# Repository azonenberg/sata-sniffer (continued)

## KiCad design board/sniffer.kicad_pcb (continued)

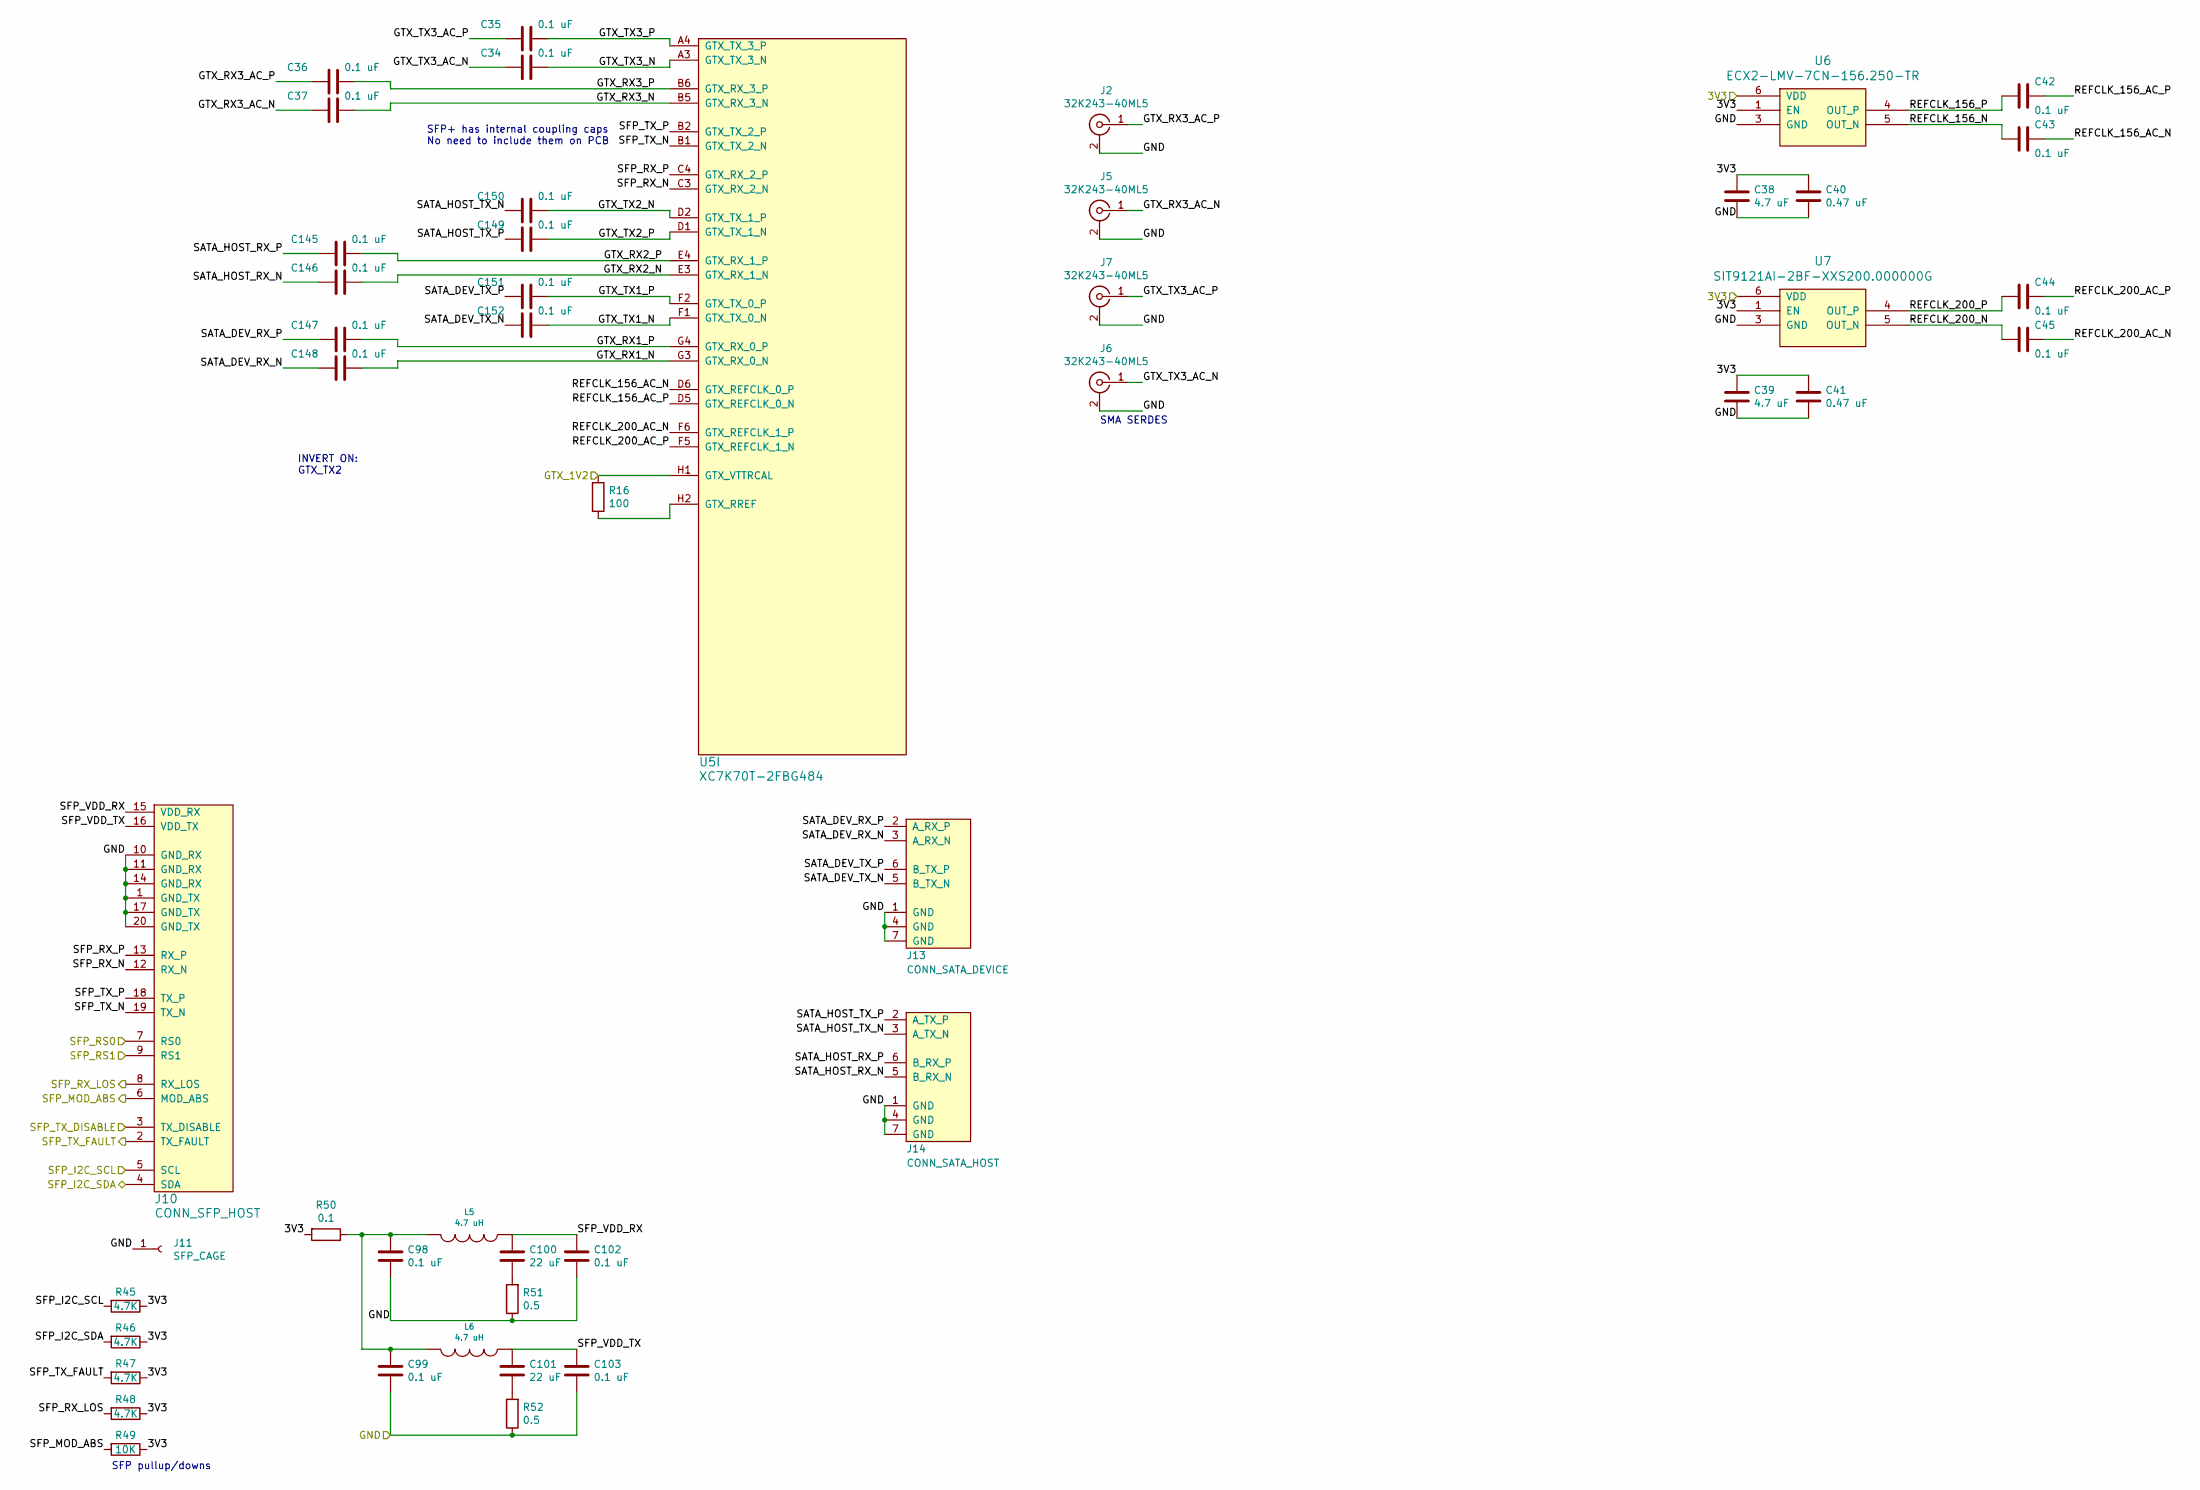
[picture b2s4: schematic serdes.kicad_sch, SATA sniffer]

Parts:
C34, C35, C36, C37, C42, C43, C44, C45, C98, C99, C102, C103, C145, C146, C147, C148, C149, C150, C151, C152: 0.1 uF; EIA_0402_CAP_NOSILK
C38, C39: 4.7 uF; EIA_0603_CAP_NOSILK
C40, C41: 0.47 uF; EIA_0402_CAP_NOSILK
C100, C101: 22 uF; EIA_1206_CAP_NOSILK
J2, J5, J6, J7: 32K243-40ML5; CONN_SMA_EDGE_ROSENBERGER_32K243_40ML5
J10: CONN_SFP_HOST; CONN_SFP+_AMPHENOL_UE76_A10_2000T
J11: SFP_CAGE; CONN_SFP_CAGE_TE_2007194-1
J13: CONN_SATA_DEVICE; CONN_SATA_MOLEX_0674901220
J14: CONN_SATA_HOST; CONN_SATA_MOLEX_0674901220
L5, L6: 4.7 uH; EIA_0805_INDUCTOR_NOSILK
R16: 100; EIA_0402_RES_NOSILK
R45, R46, R47, R48: 4.7K; EIA_0402_RES_NOSILK
R49: 10K; EIA_0402_RES_NOSILK
R50: 0.1; EIA_0402_RES_NOSILK
R51, R52: 0.5; EIA_0402_RES_NOSILK
U5: XC7K70T-2FBG484; BGA_484_22x22_FULLARRAY_1MM
U6: ECX2-LMV-7CN-156.250-TR; OSCILLATOR_LVDS_7.0x5.0
U7: SIT9121AI-2BF-XXS200.000000G; OSCILLATOR_LVDS_3.2x2.5

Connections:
/3.3V I/O/SFP_MOD_ABS: J10.6 (MOD_ABS), R49.2; also elsewhere on the board
/3.3V I/O/SFP_RS0: J10.7 (RS0); also elsewhere on the board
/3.3V I/O/SFP_RS1: J10.9 (RS1); also elsewhere on the board
/3.3V I/O/SFP_RX_LOS: J10.8 (RX_LOS), R48.2; also elsewhere on the board
/3.3V I/O/SFP_TX_DISABLE: J10.3 (TX_DISABLE); also elsewhere on the board
/3.3V I/O/SFP_TX_FAULT: J10.2 (TX_FAULT), R47.2; also elsewhere on the board
/3V3: C38.1, C39.1, C40.1, C41.1, R45.1, R46.1, R47.1, R48.1, R49.1, R50.2, U6.1 (EN), U6.6 (VDD), U7.1 (EN), U7.6 (VDD); also elsewhere on the board
/GTX_1V2: R16.1, U5.H1 (GTX_VTTRCAL); also elsewhere on the board
/SERDES interfaces/GTX_RX1_N: C148.1, U5.G3 (GTX_RX_0_N)
/SERDES interfaces/GTX_RX1_P: C147.1, U5.G4 (GTX_RX_0_P)
/SERDES interfaces/GTX_RX2_N: C146.1, U5.E3 (GTX_RX_1_N)
/SERDES interfaces/GTX_RX2_P: C145.1, U5.E4 (GTX_RX_1_P)
/SERDES interfaces/GTX_RX3_AC_N: C37.2, J5.1 (In)
/SERDES interfaces/GTX_RX3_AC_P: C36.2, J2.1 (In)
/SERDES interfaces/GTX_RX3_N: C37.1, U5.B5 (GTX_RX_3_N)
/SERDES interfaces/GTX_RX3_P: C36.1, U5.B6 (GTX_RX_3_P)
/SERDES interfaces/GTX_TX1_N: C152.1, U5.F1 (GTX_TX_0_N)
/SERDES interfaces/GTX_TX1_P: C151.1, U5.F2 (GTX_TX_0_P)
/SERDES interfaces/GTX_TX2_N: C150.1, U5.D2 (GTX_TX_1_P)
/SERDES interfaces/GTX_TX2_P: C149.1, U5.D1 (GTX_TX_1_N)
/SERDES interfaces/GTX_TX3_AC_N: C34.2, J6.1 (In)
/SERDES interfaces/GTX_TX3_AC_P: C35.2, J7.1 (In)
/SERDES interfaces/GTX_TX3_N: C34.1, U5.A3 (GTX_TX_3_N)
/SERDES interfaces/GTX_TX3_P: C35.1, U5.A4 (GTX_TX_3_P)
/SERDES interfaces/REFCLK_156_AC_N: C43.1, U5.D6 (GTX_REFCLK_0_P)
/SERDES interfaces/REFCLK_156_AC_P: C42.1, U5.D5 (GTX_REFCLK_0_N)
/SERDES interfaces/REFCLK_156_N: C43.2, U6.5 (OUT_N)
/SERDES interfaces/REFCLK_156_P: C42.2, U6.4 (OUT_P)
/SERDES interfaces/REFCLK_200_AC_N: C45.1, U5.F6 (GTX_REFCLK_1_P)
/SERDES interfaces/REFCLK_200_AC_P: C44.1, U5.F5 (GTX_REFCLK_1_N)
/SERDES interfaces/REFCLK_200_N: C45.2, U7.5 (OUT_N)
/SERDES interfaces/REFCLK_200_P: C44.2, U7.4 (OUT_P)
/SERDES interfaces/SATA_DEV_RX_N: C148.2, J13.3 (A_RX_N)
/SERDES interfaces/SATA_DEV_RX_P: C147.2, J13.2 (A_RX_P)
/SERDES interfaces/SATA_DEV_TX_N: C152.2, J13.5 (B_TX_N)
/SERDES interfaces/SATA_DEV_TX_P: C151.2, J13.6 (B_TX_P)
/SERDES interfaces/SATA_HOST_RX_N: C146.2, J14.5 (B_RX_N)
/SERDES interfaces/SATA_HOST_RX_P: C145.2, J14.6 (B_RX_P)
/SERDES interfaces/SATA_HOST_TX_N: C150.2, J14.3 (A_TX_N)
/SERDES interfaces/SATA_HOST_TX_P: C149.2, J14.2 (A_TX_P)
/SERDES interfaces/SFP_I2C_SCL: J10.5 (SCL), R45.2; also elsewhere on the board
/SERDES interfaces/SFP_I2C_SDA: J10.4 (SDA), R46.2; also elsewhere on the board
/SERDES interfaces/SFP_RX_N: J10.12 (RX_N), U5.C3 (GTX_RX_2_N)
/SERDES interfaces/SFP_RX_P: J10.13 (RX_P), U5.C4 (GTX_RX_2_P)
/SERDES interfaces/SFP_TX_N: J10.19 (TX_N), U5.B1 (GTX_TX_2_N)
/SERDES interfaces/SFP_TX_P: J10.18 (TX_P), U5.B2 (GTX_TX_2_P)
/SERDES interfaces/SFP_VDD_RX: C100.1, C102.1, J10.15 (VDD_RX), L5.1
/SERDES interfaces/SFP_VDD_TX: C101.1, C103.1, J10.16 (VDD_TX), L6.1
unnamed: C98.1, C99.1, L5.2, L6.2, R50.1
unnamed: C100.2, R51.2
unnamed: C101.2, R52.2
unnamed: R16.2, U5.H2 (GTX_RREF)

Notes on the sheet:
SMA SERDES
SFP+ has internal coupling caps No need to include them on PCB
INVERT ON: GTX_TX2
SFP pullup/downs

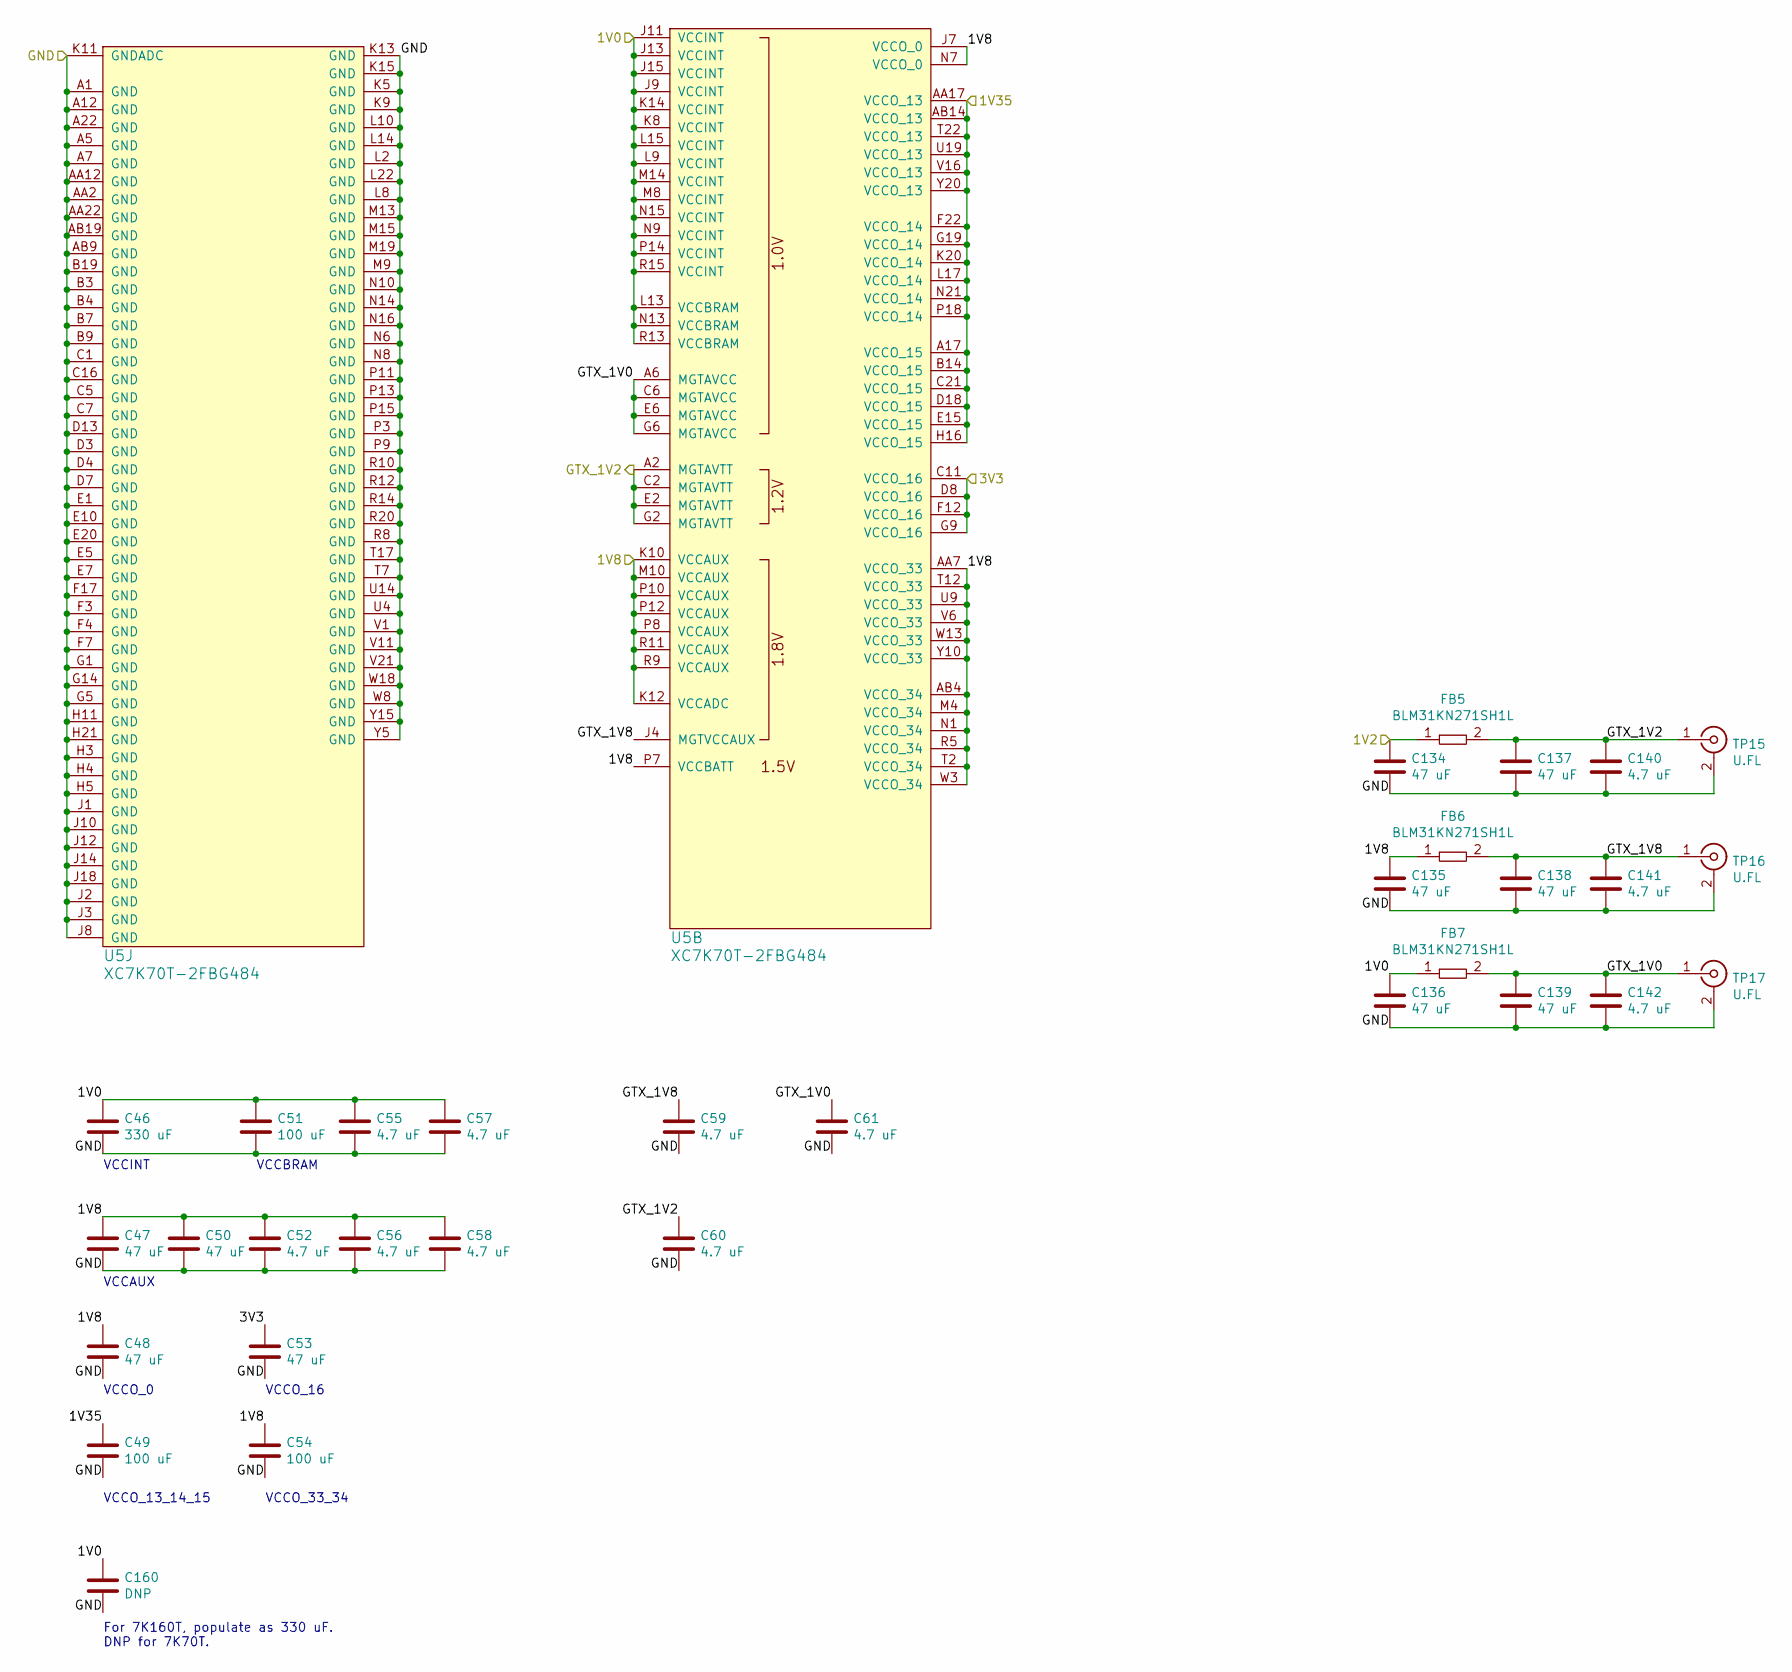
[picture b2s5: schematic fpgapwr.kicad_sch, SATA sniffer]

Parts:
C46: 330 uF; EIA_1210_CAP_NOSILK
C47, C48, C50: 47 uF; EIA_0805_CAP_NOSILK
C49, C51, C54: 100 uF; EIA_1206_CAP_NOSILK
C52, C55, C56, C57, C58, C59, C60, C61, C140, C141, C142: 4.7 uF; EIA_0603_CAP_NOSILK
C53: 47 uF; EIA_1206_CAP_NOSILK
C134, C135, C136, C137, C138, C139: 47 uF; EIA_1210_CAP_NOSILK
C160: DNP; EIA_1210_CAP_NOSILK
FB5, FB6, FB7: BLM31KN271SH1L; EIA_1206_CAP_NOSILK
TP15, TP16, TP17: U.FL; CONN_U.FL_TE_1909763-1
U5: XC7K70T-2FBG484; BGA_484_22x22_FULLARRAY_1MM

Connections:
/1V0: C46.1, C51.1, C55.1, C57.1, C136.1, C160.1, FB7.1, U5.J9 (VCCINT), U5.J11 (VCCINT), U5.J13 (VCCINT), U5.J15 (VCCINT), U5.K8 (VCCINT), U5.K14 (VCCINT), U5.L9 (VCCINT), U5.L13 (VCCBRAM), U5.L15 (VCCINT), U5.M8 (VCCINT), U5.M14 (VCCINT), U5.N9 (VCCINT), U5.N13 (VCCBRAM), U5.N15 (VCCINT), U5.P14 (VCCINT), U5.R13 (VCCBRAM), U5.R15 (VCCINT); also elsewhere on the board
/1V2: C134.1, FB5.1; also elsewhere on the board
/1V8: C47.1, C48.1, C50.1, C52.1, C54.1, C56.1, C58.1, C135.1, FB6.1, U5.AA7 (VCCO_33), U5.AB4 (VCCO_34), U5.J7 (VCCO_0), U5.K10 (VCCAUX), U5.K12 (VCCADC), U5.M4 (VCCO_34), U5.M10 (VCCAUX), U5.N1 (VCCO_34), U5.N7 (VCCO_0), U5.P7 (VCCBATT), U5.P8 (VCCAUX), U5.P10 (VCCAUX), U5.P12 (VCCAUX), U5.R5 (VCCO_34), U5.R9 (VCCAUX), U5.R11 (VCCAUX), U5.T2 (VCCO_34), U5.T12 (VCCO_33), U5.U9 (VCCO_33), U5.V6 (VCCO_33), U5.W3 (VCCO_34), U5.W13 (VCCO_33), U5.Y10 (VCCO_33); also elsewhere on the board
/1V35: C49.1, U5.A17 (VCCO_15), U5.AA17 (VCCO_13), U5.AB14 (VCCO_13), U5.B14 (VCCO_15), U5.C21 (VCCO_15), U5.D18 (VCCO_15), U5.E15 (VCCO_15), U5.F22 (VCCO_14), U5.G19 (VCCO_14), U5.H16 (VCCO_15), U5.K20 (VCCO_14), U5.L17 (VCCO_14), U5.N21 (VCCO_14), U5.P18 (VCCO_14), U5.T22 (VCCO_13), U5.U19 (VCCO_13), U5.V16 (VCCO_13), U5.Y20 (VCCO_13); also elsewhere on the board
/3V3: C53.1, U5.C11 (VCCO_16), U5.D8 (VCCO_16), U5.F12 (VCCO_16), U5.G9 (VCCO_16); also elsewhere on the board
/FPGA power/GTX_1V0: C61.1, C139.1, C142.1, FB7.2, TP17.1 (In), U5.A6 (MGTAVCC), U5.C6 (MGTAVCC), U5.E6 (MGTAVCC), U5.G6 (MGTAVCC)
/FPGA power/GTX_1V8: C59.1, C138.1, C141.1, FB6.2, TP16.1 (In), U5.J4 (MGTVCCAUX)
/GTX_1V2: C60.1, C137.1, C140.1, FB5.2, TP15.1 (In), U5.A2 (MGTAVTT), U5.C2 (MGTAVTT), U5.E2 (MGTAVTT), U5.G2 (MGTAVTT); also elsewhere on the board

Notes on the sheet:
VCCINT
VCCBRAM
VCCO_16
For 7K160T, populate as 330 uF. DNP for 7K70T.
VCCAUX
VCCO_0
VCCO_13_14_15
VCCO_33_34

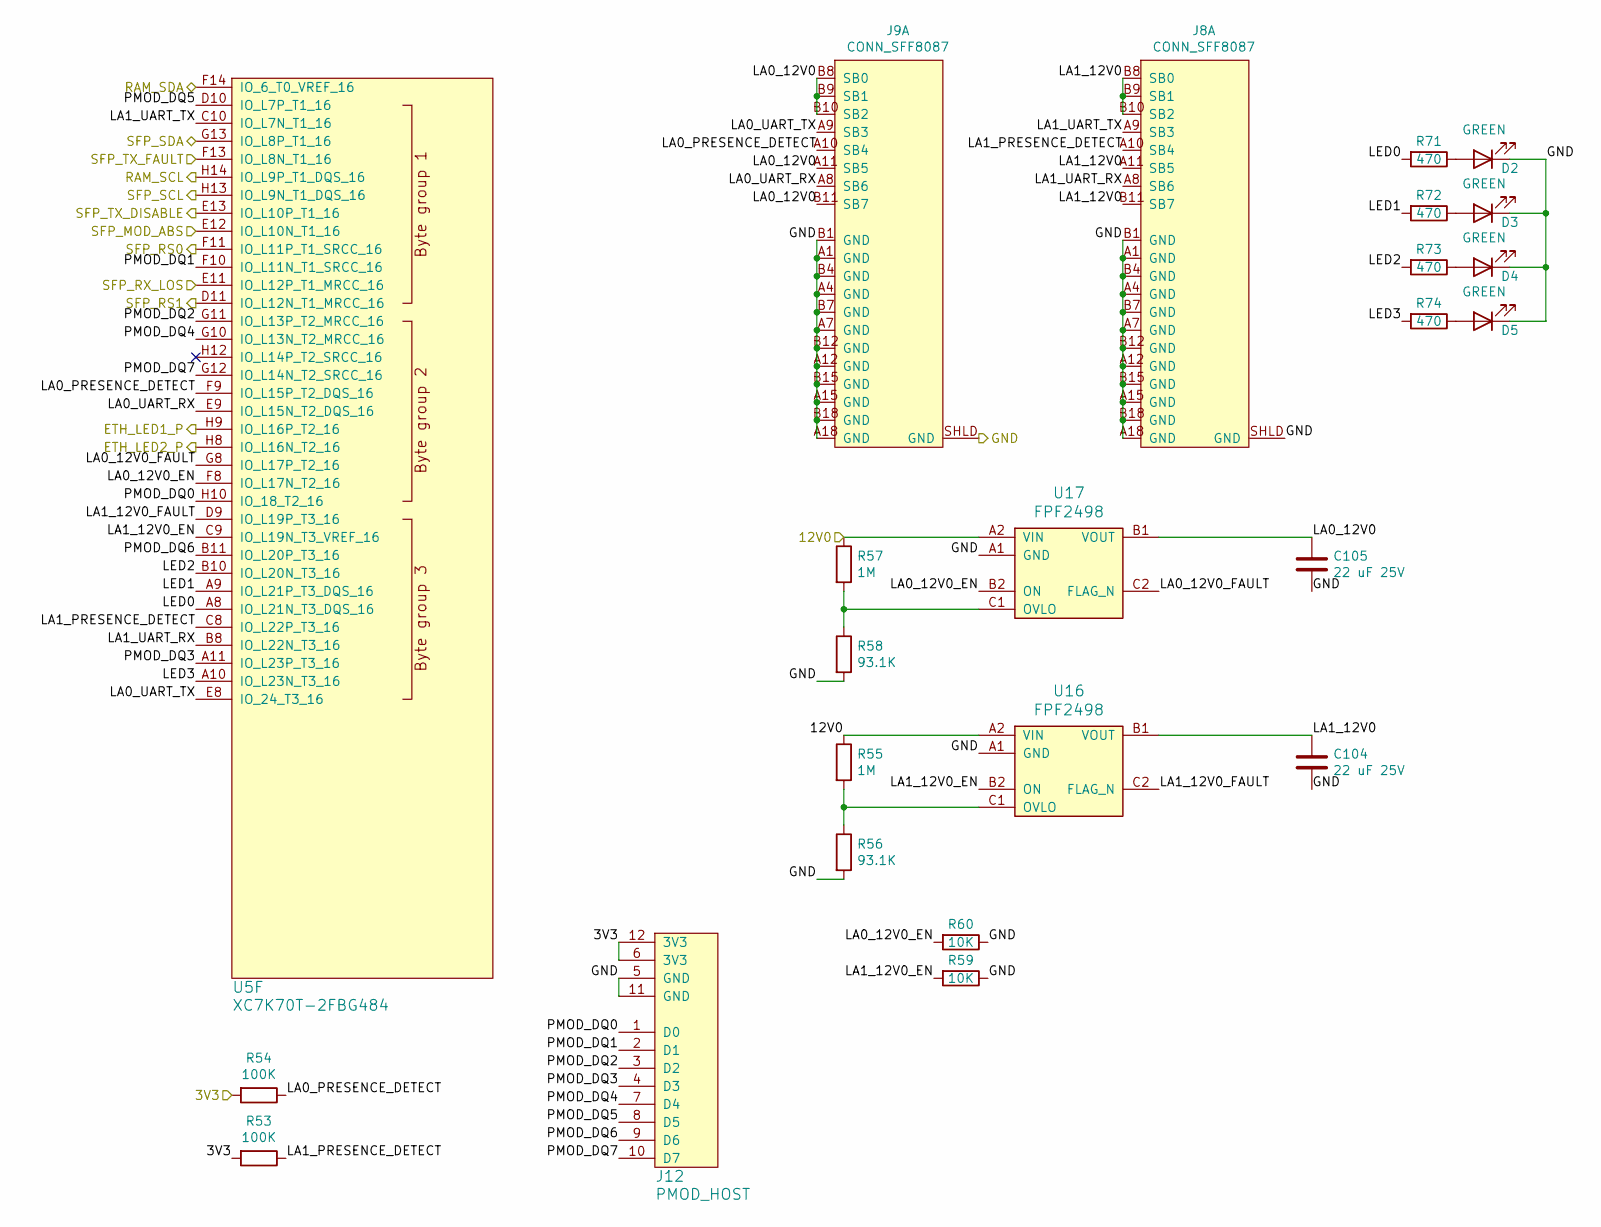
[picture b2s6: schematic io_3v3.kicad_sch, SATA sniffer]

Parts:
C104, C105: 22 uF 25V; EIA_1812_CAP_NOSILK
D2, D3, D4, D5: GREEN; EIA_0402_LED
J8, J9: CONN_SFF8087; CONN_SFF8087_MOLEX_75783-0140
J12: PMOD_HOST; CONN_HEADER_2.54MM_2x6_RA_PMOD_HOST
R53, R54: 100K; EIA_0402_RES_NOSILK
R55, R57: 1M; EIA_0402_RES_NOSILK
R56, R58: 93.1K; EIA_0402_RES_NOSILK
R59, R60: 10K; EIA_0402_RES_NOSILK
R71, R72, R73, R74: 470; EIA_0402_RES_NOSILK
U5: XC7K70T-2FBG484; BGA_484_22x22_FULLARRAY_1MM
U16, U17: FPF2498; BGA_6_1.3x1.0_0.4MM

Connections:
/3.3V I/O/ETH_LED1_P: U5.H9 (IO_L16P_T2_16); also elsewhere on the board
/3.3V I/O/ETH_LED2_P: U5.H8 (IO_L16N_T2_16); also elsewhere on the board
/3.3V I/O/LA0_12V0: C105.1, J9.A11 (SB5), J9.B8 (SB0), J9.B9 (SB1), J9.B10 (SB2), J9.B11 (SB7), U17.B1 (VOUT)
/3.3V I/O/LA0_12V0_EN: R60.2, U5.F8 (IO_L17N_T2_16), U17.B2 (ON)
/3.3V I/O/LA0_12V0_FAULT: U5.G8 (IO_L17P_T2_16), U17.C2 (FLAG_N)
/3.3V I/O/LA0_PRESENCE_DETECT: J9.A10 (SB4), R54.1, U5.F9 (IO_L15P_T2_DQS_16)
/3.3V I/O/LA0_UART_RX: J9.A8 (SB6), U5.E9 (IO_L15N_T2_DQS_16)
/3.3V I/O/LA0_UART_TX: J9.A9 (SB3), U5.E8 (IO_24_T3_16)
/3.3V I/O/LA1_12V0: C104.1, J8.A11 (SB5), J8.B8 (SB0), J8.B9 (SB1), J8.B10 (SB2), J8.B11 (SB7), U16.B1 (VOUT)
/3.3V I/O/LA1_12V0_EN: R59.2, U5.C9 (IO_L19N_T3_VREF_16), U16.B2 (ON)
/3.3V I/O/LA1_12V0_FAULT: U5.D9 (IO_L19P_T3_16), U16.C2 (FLAG_N)
/3.3V I/O/LA1_PRESENCE_DETECT: J8.A10 (SB4), R53.1, U5.C8 (IO_L22P_T3_16)
/3.3V I/O/LA1_UART_RX: J8.A8 (SB6), U5.B8 (IO_L22N_T3_16)
/3.3V I/O/LA1_UART_TX: J8.A9 (SB3), U5.C10 (IO_L7N_T1_16)
/3.3V I/O/LED0: R71.2, U5.A8 (IO_L21N_T3_DQS_16)
/3.3V I/O/LED1: R72.2, U5.A9 (IO_L21P_T3_DQS_16)
/3.3V I/O/LED2: R73.2, U5.B10 (IO_L20N_T3_16)
/3.3V I/O/LED3: R74.2, U5.A10 (IO_L23N_T3_16)
/3.3V I/O/PMOD_DQ0: J12.1 (D0), U5.H10 (IO_18_T2_16)
/3.3V I/O/PMOD_DQ1: J12.2 (D1), U5.F10 (IO_L11N_T1_SRCC_16)
/3.3V I/O/PMOD_DQ2: J12.3 (D2), U5.G11 (IO_L13P_T2_MRCC_16)
/3.3V I/O/PMOD_DQ3: J12.4 (D3), U5.A11 (IO_L23P_T3_16)
/3.3V I/O/PMOD_DQ4: J12.7 (D4), U5.G10 (IO_L13N_T2_MRCC_16)
/3.3V I/O/PMOD_DQ5: J12.8 (D5), U5.D10 (IO_L7P_T1_16)
/3.3V I/O/PMOD_DQ6: J12.9 (D6), U5.B11 (IO_L20P_T3_16)
/3.3V I/O/PMOD_DQ7: J12.10 (D7), U5.G12 (IO_L14N_T2_SRCC_16)
/3.3V I/O/SFP_MOD_ABS: U5.E12 (IO_L10N_T1_16); also elsewhere on the board
/3.3V I/O/SFP_RS0: U5.F11 (IO_L11P_T1_SRCC_16); also elsewhere on the board
/3.3V I/O/SFP_RS1: U5.D11 (IO_L12N_T1_MRCC_16); also elsewhere on the board
/3.3V I/O/SFP_RX_LOS: U5.E11 (IO_L12P_T1_MRCC_16); also elsewhere on the board
/3.3V I/O/SFP_TX_DISABLE: U5.E13 (IO_L10P_T1_16); also elsewhere on the board
/3.3V I/O/SFP_TX_FAULT: U5.F13 (IO_L8N_T1_16); also elsewhere on the board
/3V3: J12.6 (3V3), J12.12 (3V3), R53.2, R54.2; also elsewhere on the board
/12V0: R55.1, R57.1, U16.A2 (VIN), U17.A2 (VIN); also elsewhere on the board
/RAM_SCL: U5.H14 (IO_L9P_T1_DQS_16); also elsewhere on the board
/RAM_SDA: U5.F14 (IO_6_T0_VREF_16); also elsewhere on the board
/SERDES interfaces/SFP_I2C_SCL: U5.H13 (IO_L9N_T1_DQS_16); also elsewhere on the board
/SERDES interfaces/SFP_I2C_SDA: U5.G13 (IO_L8P_T1_16); also elsewhere on the board
unnamed: D2.2 (A), R71.1
unnamed: D3.2 (A), R72.1
unnamed: D4.2 (A), R73.1
unnamed: D5.2 (A), R74.1
unnamed: R55.2, R56.1, U16.C1 (OVLO)
unnamed: R57.2, R58.1, U17.C1 (OVLO)

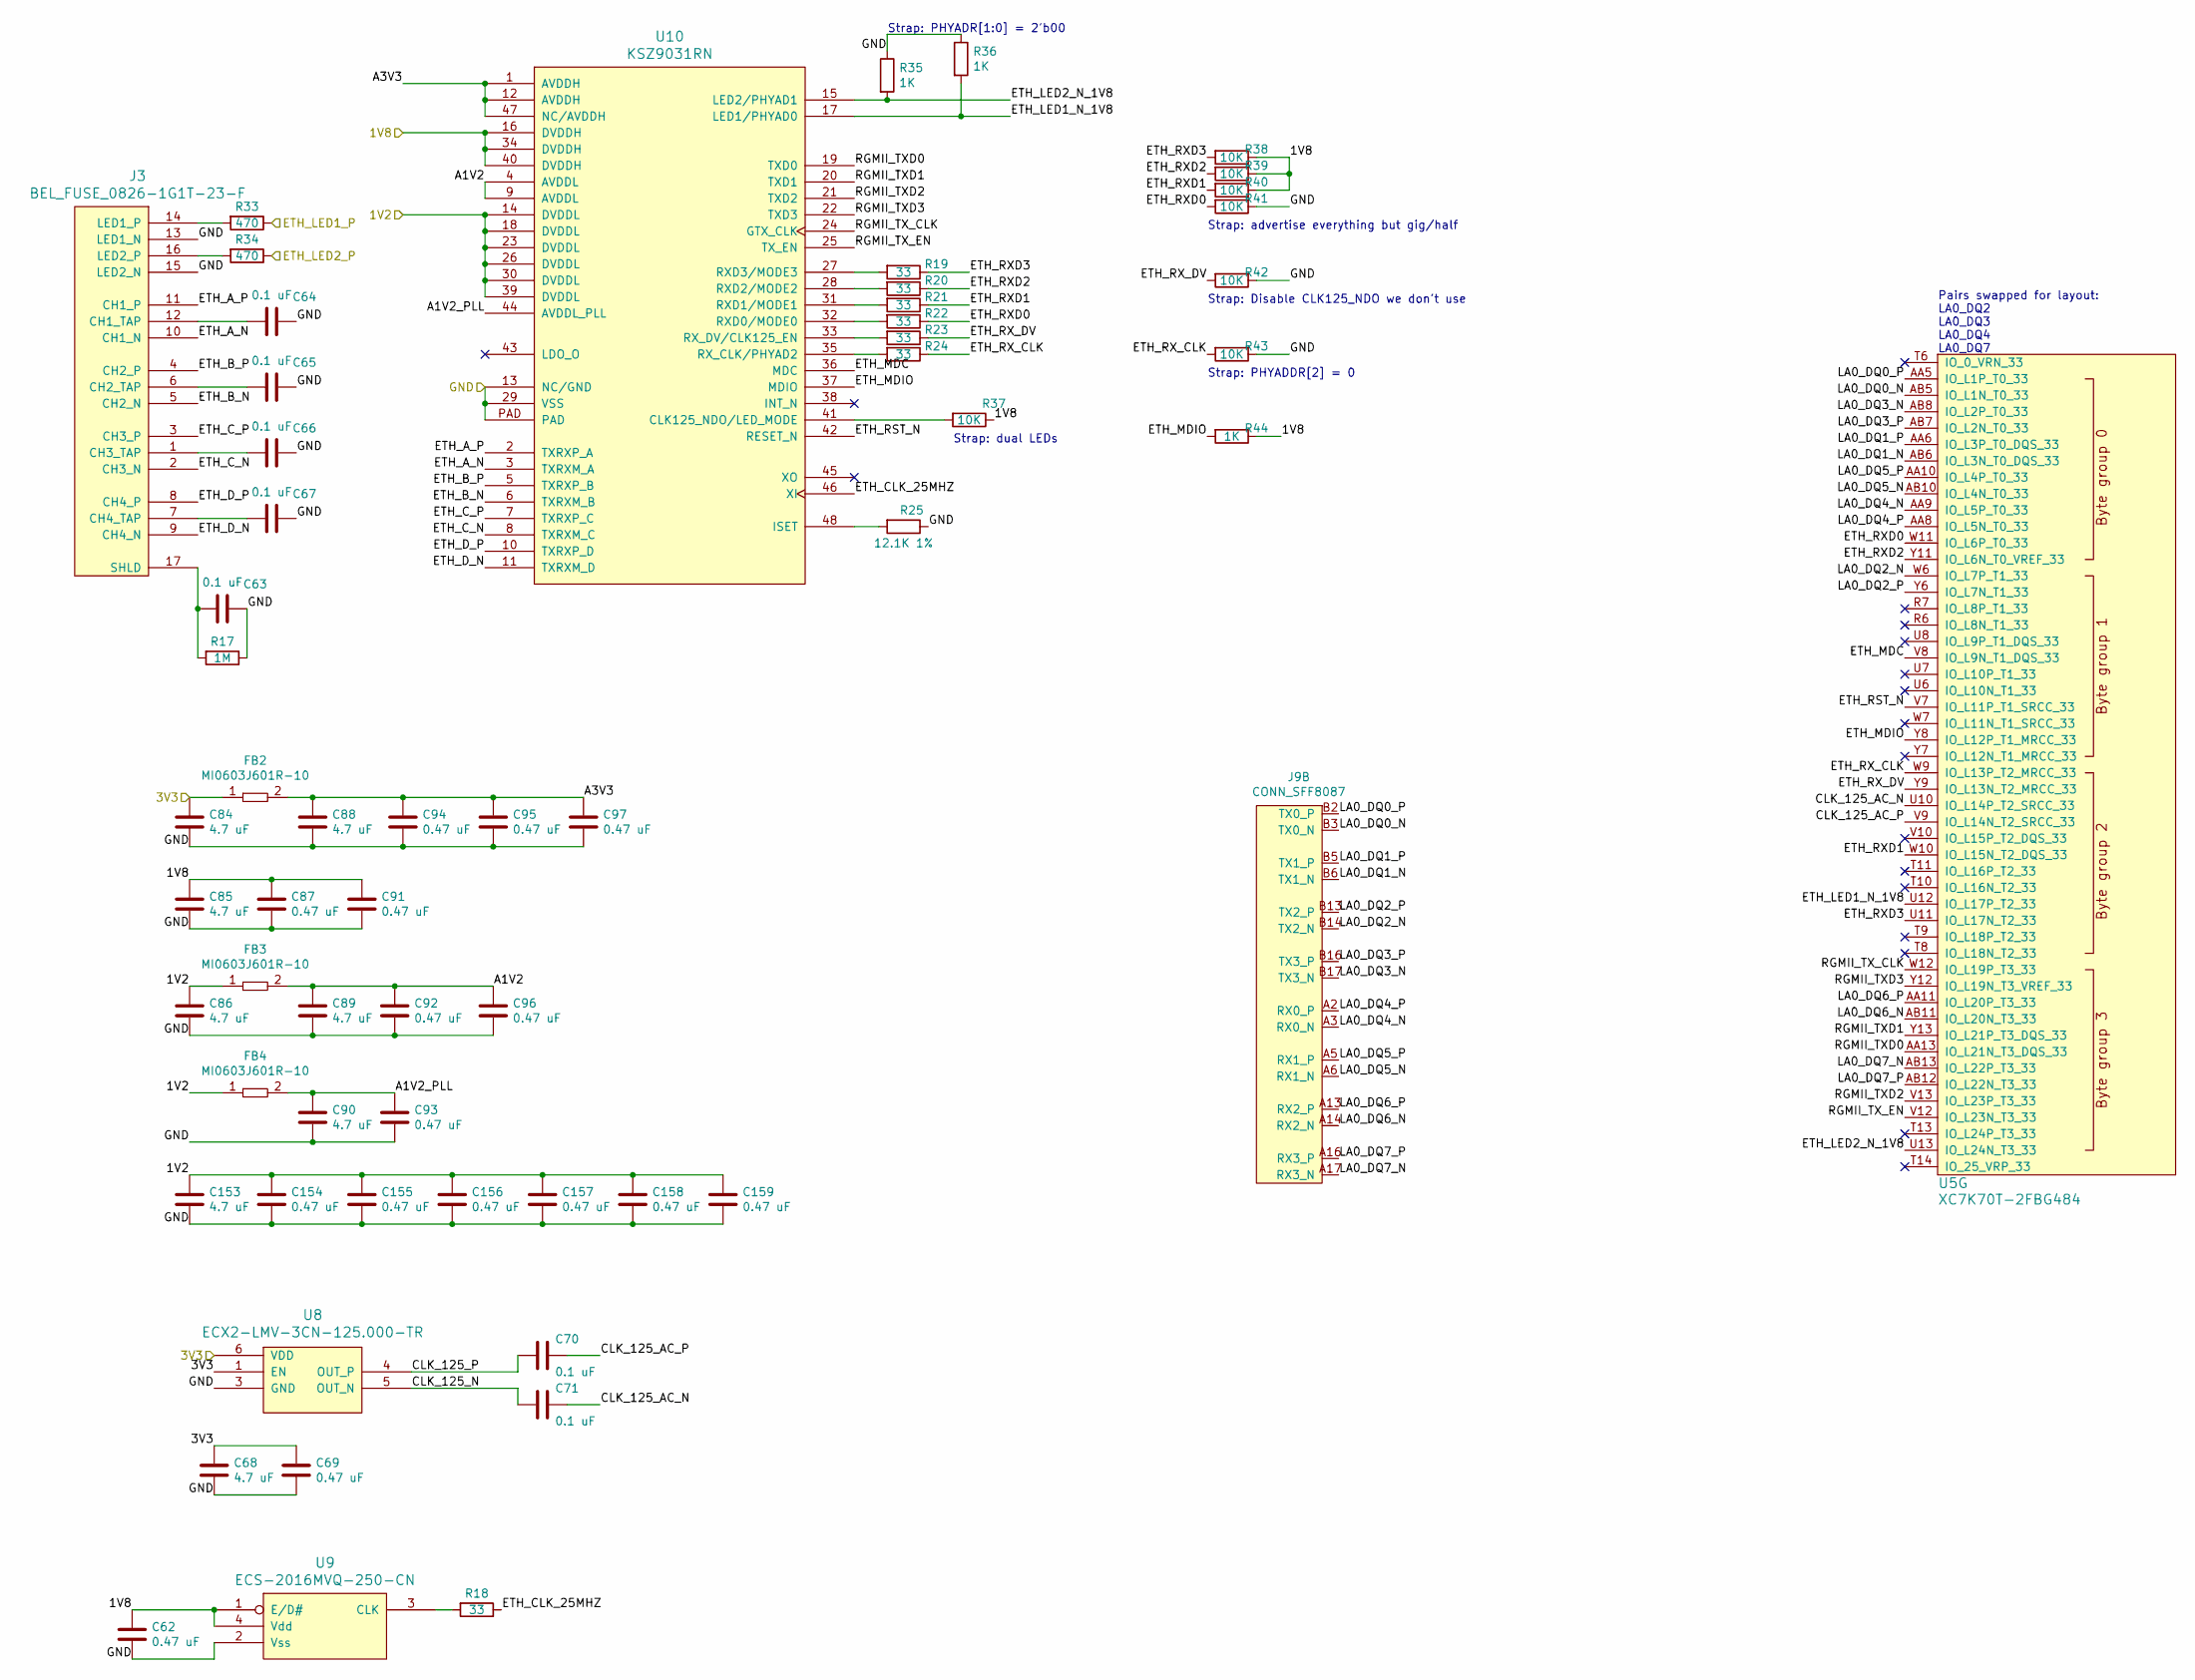
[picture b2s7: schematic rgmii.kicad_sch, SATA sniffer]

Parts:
C62, C69, C87, C91, C92, C93, C94, C95, C96, C97, C154, C155, C156, C157, C158, C159: 0.47 uF; EIA_0402_CAP_NOSILK
C63, C64, C65, C66, C67, C70, C71: 0.1 uF; EIA_0402_CAP_NOSILK
C68, C84, C85, C86, C88, C89, C90, C153: 4.7 uF; EIA_0603_CAP_NOSILK
FB2, FB3, FB4: MI0603J601R-10; EIA_0603_INDUCTOR_NOSILK
J3: BEL_FUSE_0826-1G1T-23-F; CONN_BELFUSE_0826_1G1T_23_F
J9: CONN_SFF8087; CONN_SFF8087_MOLEX_75783-0140
R17: 1M; EIA_0402_RES_NOSILK
R18, R19, R20, R21, R22, R23, R24: 33; EIA_0402_RES_NOSILK
R25: 12.1K 1%; EIA_0402_RES_NOSILK
R33, R34: 470; EIA_0402_RES_NOSILK
R35, R36, R44: 1K; EIA_0402_RES_NOSILK
R37, R38, R39, R40, R41, R42, R43: 10K; EIA_0402_RES_NOSILK
U5: XC7K70T-2FBG484; BGA_484_22x22_FULLARRAY_1MM
U8: ECX2-LMV-3CN-125.000-TR; OSCILLATOR_LVDS_3.2x2.5
U9: ECS-2016MVQ-250-CN; OSCILLATOR_2.0x1.6
U10: KSZ9031RN; QFN_48_0.5MM_7x7MM

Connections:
/1V2: C86.1, C153.1, C154.1, C155.1, C156.1, C157.1, C158.1, C159.1, FB3.1, FB4.1, U10.14 (DVDDL), U10.18 (DVDDL), U10.23 (DVDDL), U10.26 (DVDDL), U10.30 (DVDDL), U10.39 (DVDDL); also elsewhere on the board
/1V8: C62.1, C85.1, C87.1, C91.1, R37.1, R38.1, R39.1, R40.1, R44.1, U9.1 (E/D#), U9.4 (Vdd), U10.16 (DVDDH), U10.34 (DVDDH), U10.40 (DVDDH); also elsewhere on the board
/3.3V I/O/ETH_LED1_P: R33.1; also elsewhere on the board
/3.3V I/O/ETH_LED2_P: R34.1; also elsewhere on the board
/3V3: C68.1, C69.1, C84.1, FB2.1, U8.1 (EN), U8.6 (VDD); also elsewhere on the board
/RGMII PHY/A1V2: C89.1, C92.1, C96.1, FB3.2, U10.4 (AVDDL), U10.9 (AVDDL)
/RGMII PHY/A1V2_PLL: C90.1, C93.1, FB4.2, U10.44 (AVDDL_PLL)
/RGMII PHY/A3V3: C88.1, C94.1, C95.1, C97.1, FB2.2, U10.1 (AVDDH), U10.12 (AVDDH), U10.47 (NC/AVDDH)
/RGMII PHY/CLK_125_AC_N: C71.1, U5.U10 (IO_L14P_T2_SRCC_33)
/RGMII PHY/CLK_125_AC_P: C70.1, U5.V9 (IO_L14N_T2_SRCC_33)
/RGMII PHY/CLK_125_N: C71.2, U8.5 (OUT_N)
/RGMII PHY/CLK_125_P: C70.2, U8.4 (OUT_P)
/RGMII PHY/ETH_A_N: J3.10 (CH1_N), U10.3 (TXRXM_A)
/RGMII PHY/ETH_A_P: J3.11 (CH1_P), U10.2 (TXRXP_A)
/RGMII PHY/ETH_B_N: J3.5 (CH2_N), U10.6 (TXRXM_B)
/RGMII PHY/ETH_B_P: J3.4 (CH2_P), U10.5 (TXRXP_B)
/RGMII PHY/ETH_CLK_25MHZ: R18.1, U10.46 (XI)
/RGMII PHY/ETH_C_N: J3.2 (CH3_N), U10.8 (TXRXM_C)
/RGMII PHY/ETH_C_P: J3.3 (CH3_P), U10.7 (TXRXP_C)
/RGMII PHY/ETH_D_N: J3.9 (CH4_N), U10.11 (TXRXM_D)
/RGMII PHY/ETH_D_P: J3.8 (CH4_P), U10.10 (TXRXP_D)
/RGMII PHY/ETH_LED1_N_1V8: R36.2, U5.U12 (IO_L17P_T2_33), U10.17 (LED1/PHYAD0)
/RGMII PHY/ETH_LED2_N_1V8: R35.2, U5.U13 (IO_L24N_T3_33), U10.15 (LED2/PHYAD1)
/RGMII PHY/ETH_MDC: U5.V8 (IO_L9N_T1_DQS_33), U10.36 (MDC)
/RGMII PHY/ETH_MDIO: R44.2, U5.Y8 (IO_L12P_T1_MRCC_33), U10.37 (MDIO)
/RGMII PHY/ETH_RST_N: U5.V7 (IO_L11P_T1_SRCC_33), U10.42 (RESET_N)
/RGMII PHY/ETH_RXD0: R22.1, R41.2, U5.W11 (IO_L6P_T0_33)
/RGMII PHY/ETH_RXD1: R21.1, R40.2, U5.W10 (IO_L15N_T2_DQS_33)
/RGMII PHY/ETH_RXD2: R20.1, R39.2, U5.Y11 (IO_L6N_T0_VREF_33)
/RGMII PHY/ETH_RXD3: R19.1, R38.2, U5.U11 (IO_L17N_T2_33)
/RGMII PHY/ETH_RX_CLK: R24.1, R43.2, U5.W9 (IO_L13P_T2_MRCC_33)
/RGMII PHY/ETH_RX_DV: R23.1, R42.2, U5.Y9 (IO_L13N_T2_MRCC_33)
/RGMII PHY/LA0_DQ0_N: J9.B3 (TX0_N), U5.AB5 (IO_L1N_T0_33)
/RGMII PHY/LA0_DQ0_P: J9.B2 (TX0_P), U5.AA5 (IO_L1P_T0_33)
/RGMII PHY/LA0_DQ1_N: J9.B6 (TX1_N), U5.AB6 (IO_L3N_T0_DQS_33)
/RGMII PHY/LA0_DQ1_P: J9.B5 (TX1_P), U5.AA6 (IO_L3P_T0_DQS_33)
/RGMII PHY/LA0_DQ2_N: J9.B14 (TX2_N), U5.W6 (IO_L7P_T1_33)
/RGMII PHY/LA0_DQ2_P: J9.B13 (TX2_P), U5.Y6 (IO_L7N_T1_33)
/RGMII PHY/LA0_DQ3_N: J9.B17 (TX3_N), U5.AB8 (IO_L2P_T0_33)
/RGMII PHY/LA0_DQ3_P: J9.B16 (TX3_P), U5.AB7 (IO_L2N_T0_33)
/RGMII PHY/LA0_DQ4_N: J9.A3 (RX0_N), U5.AA9 (IO_L5P_T0_33)
/RGMII PHY/LA0_DQ4_P: J9.A2 (RX0_P), U5.AA8 (IO_L5N_T0_33)
/RGMII PHY/LA0_DQ5_N: J9.A6 (RX1_N), U5.AB10 (IO_L4N_T0_33)
/RGMII PHY/LA0_DQ5_P: J9.A5 (RX1_P), U5.AA10 (IO_L4P_T0_33)
/RGMII PHY/LA0_DQ6_N: J9.A14 (RX2_N), U5.AB11 (IO_L20N_T3_33)
/RGMII PHY/LA0_DQ6_P: J9.A13 (RX2_P), U5.AA11 (IO_L20P_T3_33)
/RGMII PHY/LA0_DQ7_N: J9.A17 (RX3_N), U5.AB13 (IO_L22P_T3_33)
/RGMII PHY/LA0_DQ7_P: J9.A16 (RX3_P), U5.AB12 (IO_L22N_T3_33)
/RGMII PHY/RGMII_TXD0: U5.AA13 (IO_L21N_T3_DQS_33), U10.19 (TXD0)
/RGMII PHY/RGMII_TXD1: U5.Y13 (IO_L21P_T3_DQS_33), U10.20 (TXD1)
/RGMII PHY/RGMII_TXD2: U5.V13 (IO_L23P_T3_33), U10.21 (TXD2)
/RGMII PHY/RGMII_TXD3: U5.Y12 (IO_L19N_T3_VREF_33), U10.22 (TXD3)
/RGMII PHY/RGMII_TX_CLK: U5.W12 (IO_L19P_T3_33), U10.24 (GTX_CLK)
/RGMII PHY/RGMII_TX_EN: U5.V12 (IO_L23N_T3_33), U10.25 (TX_EN)
unnamed: C63.2, J3.17 (SHLD), R17.2
unnamed: C64.2, J3.12 (CH1_TAP)
unnamed: C65.2, J3.6 (CH2_TAP)
unnamed: C66.2, J3.1 (CH3_TAP)
unnamed: C67.2, J3.7 (CH4_TAP)
unnamed: J3.14 (LED1_P), R33.2
unnamed: J3.16 (LED2_P), R34.2
unnamed: R18.2, U9.3 (CLK)
unnamed: R19.2, U10.27 (RXD3/MODE3)
unnamed: R20.2, U10.28 (RXD2/MODE2)
unnamed: R21.2, U10.31 (RXD1/MODE1)
unnamed: R22.2, U10.32 (RXD0/MODE0)
unnamed: R23.2, U10.33 (RX_DV/CLK125_EN)
unnamed: R24.2, U10.35 (RX_CLK/PHYAD2)
unnamed: R25.2, U10.48 (ISET)
unnamed: R37.2, U10.41 (CLK125_NDO/LED_MODE)

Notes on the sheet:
Strap: Disable CLK125_NDO we don't use
Strap: dual LEDs
Strap: advertise everything but gig/half
Strap: PHYADR[1:0] = 2'b00
Pairs swapped for layout: LA0_DQ2 LA0_DQ3 LA0_DQ4 LA0_DQ7
Strap: PHYADDR[2] = 0
